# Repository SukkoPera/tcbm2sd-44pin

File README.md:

# TCBM2SD 44-pin
TCBM2SD is a CBM 1551 paddle replacement and/or mass storage device using an SD card interfacing with the Commodore C16/116/Plus4 simulating a TCBM bus 1551 disk drive.

## Summary
This is a 44-pin variant of [the original project by Maciej 'YTM/Elysium' Witkowiak](https://github.com/ytmytm/plus4-tcbm2sd).

This version is still aimed at the C16/C116/Plus4 and it **requires** the usage of a [Plus4MultiExpander](https://github.com/SukkoPera/Plus4MultiExpander) or something similar. It is NOT compatible with the C64/C128.

Isn't Open Hardware great?

## Usage
This variant of the board requires the FPGA to be flashed with the JED file from this project. The corresponding sources are available in the [hdl](hdl/) directory.

Apart from that, please refer to [the original project](https://github.com/ytmytm/plus4-tcbm2sd) for documentation, instructions, etc.

## Releases
If you want to get this board produced, you are recommended to get [the latest release](https://github.com/SukkoPera/tcbm2sd-44pin/releases) rather than the current git version, as the latter might be under development and is not guaranteed to be working.

Every release is accompanied by its Bill Of Materials (BOM) file and any relevant notes about it, which you are recommended to read carefully.

## License
TCBM2SD is licensed under the [Creative Commons Attribution-ShareAlike 4.0 International License](https://creativecommons.org/licenses/by-sa/4.0/).

This documentation is distributed *as is* and WITHOUT ANY EXPRESS OR IMPLIED WARRANTIES whatsoever with respect to its functionality, operability or use, including, without limitation, any implied warranties OF MERCHANTABILITY, SATISFACTORY QUALITY, FITNESS FOR A PARTICULAR PURPOSE or infringement. We expressly disclaim any liability whatsoever for any direct, indirect, consequential, incidental or special damages, including, without limitation, lost revenues, lost profits, losses resulting from business interruption or loss of data, regardless of the form of action or legal theory under which the liability may be asserted, even if advised of the possibility or likelihood of such damages.

## Thanks
- Thanks to Maciej for his amazing work and support.
- 3D model of Arduino Pro Micro by [Toby](https://grabcad.com/library/arduino-pro-mini-5v-16mhz-1).

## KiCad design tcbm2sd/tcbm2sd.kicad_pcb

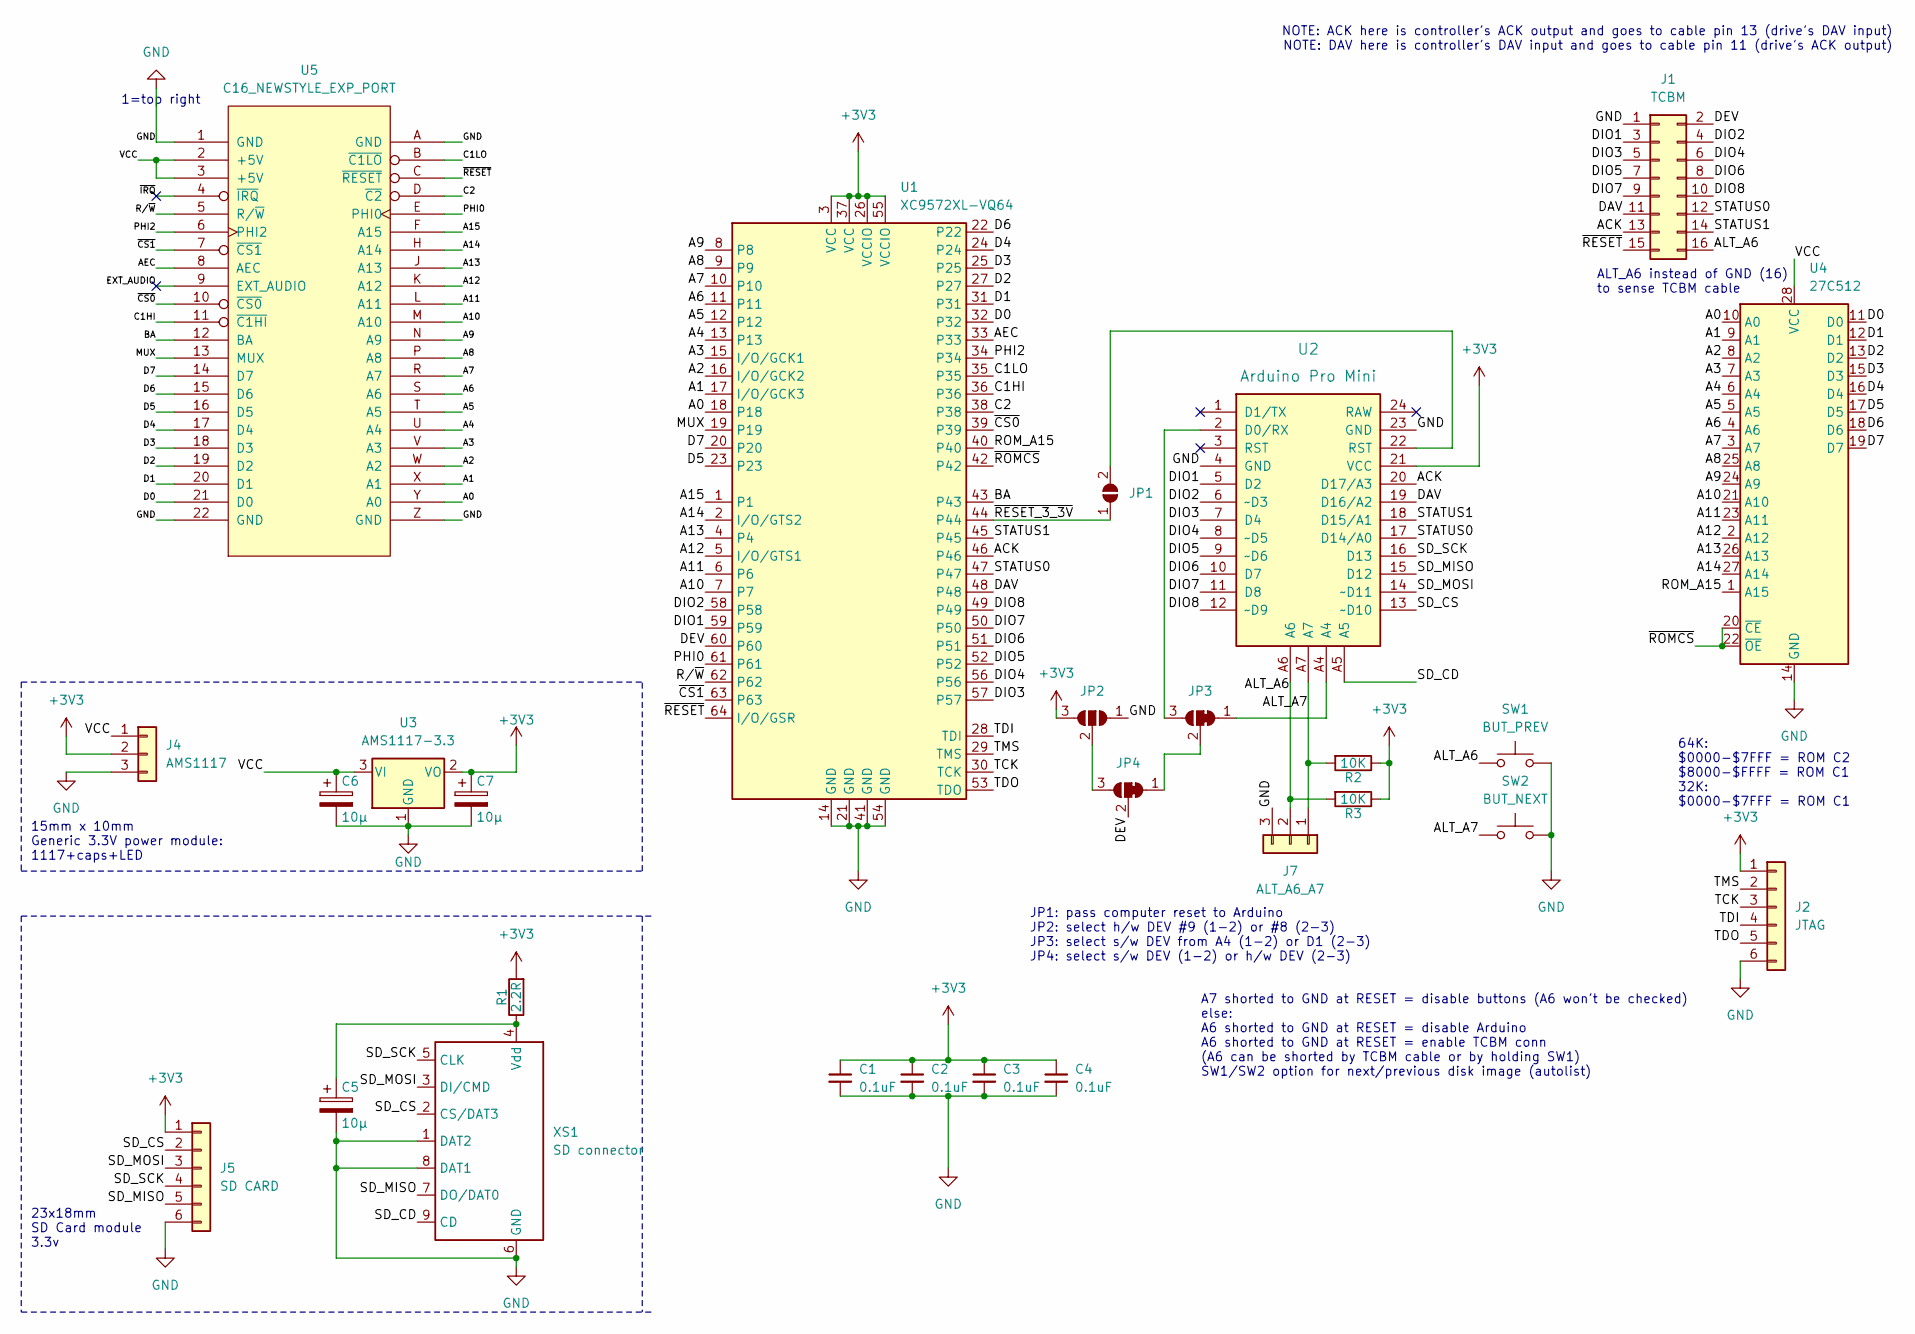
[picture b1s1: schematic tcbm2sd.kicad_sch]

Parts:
C1, C2, C3, C4: 0.1uF; C_0805_2012Metric_Pad1.18x1.45mm_HandSolder; JLCPCB Part # C49678
C5, C6, C7: 10µ; CP_EIA-3216-12_Kemet-S_Pad1.58x1.35mm_HandSolder; JLCPCB Part # C1969735
J1: TCBM; PinHeader_2x08_P2.54mm_Vertical
J2: JTAG; PinHeader_1x06_P2.54mm_Vertical
J4: AMS1117; PinHeader_1x03_P2.54mm_Vertical
J5: SD CARD; PinHeader_1x06_P2.54mm_Vertical
J7: ALT_A6_A7; PinHeader_1x03_P2.54mm_Vertical
JP1: SolderJumper_2_Open; SolderJumper-2_P1.3mm_Open_Pad1.0x1.5mm
JP2: SolderJumper_3_Open; SolderJumper-3_P1.3mm_Open_Pad1.0x1.5mm_NumberLabels
JP3, JP4: SolderJumper_3_Bridged12; SolderJumper-3_P1.3mm_Bridged12_Pad1.0x1.5mm_NumberLabels
R1: 2.2R; R_0805_2012Metric_Pad1.20x1.40mm_HandSolder; JLCPCB Part # C17521
R2, R3: 10K; R_0805_2012Metric_Pad1.20x1.40mm_HandSolder; JLCPCB Part # C17414
SW1: BUT_PREV; SW_PUSH_6mm_OR_SW_Tactile_SPST_Angled_PTS645Vx58-2LFS
SW2: BUT_NEXT; SW_PUSH_6mm_OR_SW_Tactile_SPST_Angled_PTS645Vx58-2LFS
U1: XC9572XL-VQ64; TQFP-64_10x10mm_P0.5mm; JLCPCB Part # C90569
U2: Arduino Pro Mini; Arduino_Pro_Mini
U3: AMS1117-3.3; SOT-223-3_TabPin2; JLCPCB Part # C6186
U4: 27C512; DIP-28_W15.24mm_Socket
U5: C16_NEWSTYLE_EXP_PORT; EdgeConn-44pin
XS1: SD connector; Conn_uSDcard; JLCPCB Part # C7529389

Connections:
+3V3: C1.1, C2.1, C3.1, C4.1, C7.1, J2.1, J4.2, J5.1, JP2.3 (B), R1.2, R2.1, R3.1, U1.3 (VCC), U1.26 (VCCIO), U1.37 (VCC), U1.55 (VCCIO), U2.21 (VCC), U3.2 (VO)
/A0: U1.18, U4.10 (A0), U5.Y (A0)
/A1: U1.17 (I/O/GCK3), U4.9 (A1), U5.X (A1)
/A2: U1.16 (I/O/GCK2), U4.8 (A2), U5.W (A2)
/A3: U1.15 (I/O/GCK1), U4.7 (A3), U5.V (A3)
/A4: U1.13, U4.6 (A4), U5.U (A4)
/A5: U1.12, U4.5 (A5), U5.T (A5)
/A6: U1.11, U4.4 (A6), U5.S (A6)
/A7: U1.10, U4.3 (A7), U5.R (A7)
/A8: U1.9, U4.25 (A8), U5.P (A8)
/A9: U1.8, U4.24 (A9), U5.N (A9)
/A10: U1.7, U4.21 (A10), U5.M (A10)
/A11: U1.6, U4.23 (A11), U5.L (A11)
/A12: U1.5 (I/O/GTS1), U4.2 (A12), U5.K (A12)
/A13: U1.4, U4.26 (A13), U5.J (A13)
/A14: U1.2 (I/O/GTS2), U4.27 (A14), U5.H (A14)
/A15: U1.1, U5.F (A15)
/ACK: J1.13, U1.46, U2.20 (D17/A3)
/AEC: U1.33, U5.8 (AEC)
/ALT_A6: J1.16, J7.2, R3.2, SW1.1, U2.A6
/ALT_A7: J7.1, R2.2, SW2.1, U2.A7
/BA: U1.43, U5.12 (BA)
/C1HI: U1.36, U5.11 (~C1HI)
/C1LO: U1.35, U5.B (~C1LO)
/C2: U1.38, U5.D (~C2)
/D0: U1.32, U4.11 (D0), U5.21 (D0)
/D1: U1.31, U4.12 (D1), U5.20 (D1)
/D2: U1.27, U4.13 (D2), U5.19 (D2)
/D3: U1.25, U4.15 (D3), U5.18 (D3)
/D4: U1.24, U4.16 (D4), U5.17 (D4)
/D5: U1.23, U4.17 (D5), U5.16 (D5)
/D6: U1.22, U4.18 (D6), U5.15 (D6)
/D7: U1.20, U4.19 (D7), U5.14 (D7)
/DAV: J1.11, U1.48, U2.19 (D16/A2)
/DEV: J1.2, JP4.2 (C), U1.60
/DIO1: J1.3, U1.59, U2.5 (D2)
/DIO2: J1.4, U1.58, U2.6 (~D3)
/DIO3: J1.5, U1.57, U2.7 (D4)
/DIO4: J1.6, U1.56, U2.8 (~D5)
/DIO5: J1.7, U1.52, U2.9 (~D6)
/DIO6: J1.8, U1.51, U2.10 (D7)
/DIO7: J1.9, U1.50, U2.11 (D8)
/DIO8: J1.10, U1.49, U2.12 (~D9)
/EXT_AUDIO: U5.9 (EXT_AUDIO)
/MUX: U1.19, U5.13 (MUX)
/PHI0: U1.61, U5.E (PHI0)
/PHI2: U1.34, U5.6 (PHI2)
/ROM_A15: U1.40, U4.1 (A15)
/R/~W: U1.62, U5.5 (R/~W)
/SD_CD: U2.A5, XS1.9 (CD)
/SD_CS: J5.2, U2.13 (~D10), XS1.2 (CS/DAT3)
/SD_MISO: J5.5, U2.15 (D12), XS1.7 (DO/DAT0)
/SD_MOSI: J5.3, U2.14 (~D11), XS1.3 (DI/CMD)
/SD_SCK: J5.4, U2.16 (D13), XS1.5 (CLK)
/STATUS0: J1.12, U1.47, U2.17 (D14/A0)
/STATUS1: J1.14, U1.45, U2.18 (D15/A1)
/TCK: J2.3, U1.30 (TCK)
/TDI: J2.4, U1.28 (TDI)
/TDO: J2.5, U1.53 (TDO)
/TMS: J2.2, U1.29 (TMS)
/VCC: C6.1, J4.1, U3.3 (VI), U4.28 (VCC), U5.2 (+5V), U5.3 (+5V)
/~CS0: U1.39, U5.10 (~CS0)
/~CS1: U1.63, U5.7 (~CS1)
/~IRQ: U5.4 (~IRQ)
/~RESET_3_3V: JP1.1 (A), U1.44
/~RESET: J1.15, U1.64 (I/O/GSR), U5.C (~RESET)
/~ROMCS: U1.42, U4.20 (~CE), U4.22 (~OE)
GND: C1.2, C2.2, C3.2, C4.2, C5.2, C6.2, C7.2, J1.1, J2.6, J4.3, J5.6, J7.3, JP2.1 (A), SW1.2, SW2.2, U1.14 (GND), U1.21 (GND), U1.41 (GND), U1.54 (GND), U2.4 (GND), U2.23 (GND), U3.1 (GND), U4.14 (GND), U5.1 (GND), U5.22 (GND), U5.A (GND), U5.Z (GND), XS1.1 (DAT2), XS1.6 (GND), XS1.8 (DAT1)
unnamed: JP1.2 (B), U2.22 (RST)
unnamed: JP2.2 (C), JP4.3 (B)
unnamed: JP3.1 (A), U2.A4
unnamed: JP3.3 (B), U2.2 (D0/RX)
unnamed: JP3.2 (C), JP4.1 (A)
unnamed: C5.1, R1.1, XS1.4 (Vdd)

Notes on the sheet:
ALT_A6 instead of GND (16) to sense TCBM cable
15mm x 10mm Generic 3.3V power module: 1117+caps+LED
JP1: pass computer reset to Arduino JP2: select h/w DEV #9 (1-2) or #8 (2-3) JP3: select s/w DEV from A4 (1-2) or D1 (2-3) JP4: select s/w DEV (1-2) or h/w DEV (2-3)
A7 shorted to GND at RESET = disable buttons (A6 won't be checked) else: A6 shorted to GND at RESET = disable Arduino A6 shorted to GND at RESET = enable TCBM conn (A6 can be shorted by TCBM cable or by holding SW1) SW1/SW2 option for next/previous disk image (autolist)
NOTE: ACK here is controller's ACK output and goes to cable pin 13 (drive's DAV input) NOTE: DAV here is controller's DAV input and goes to cable pin 11 (drive's ACK output)
1=top right
23x18mm SD Card module 3.3v
64K: $0000-$7FFF = ROM C2 $8000-$FFFF = ROM C1 32K: $0000-$7FFF = ROM C1

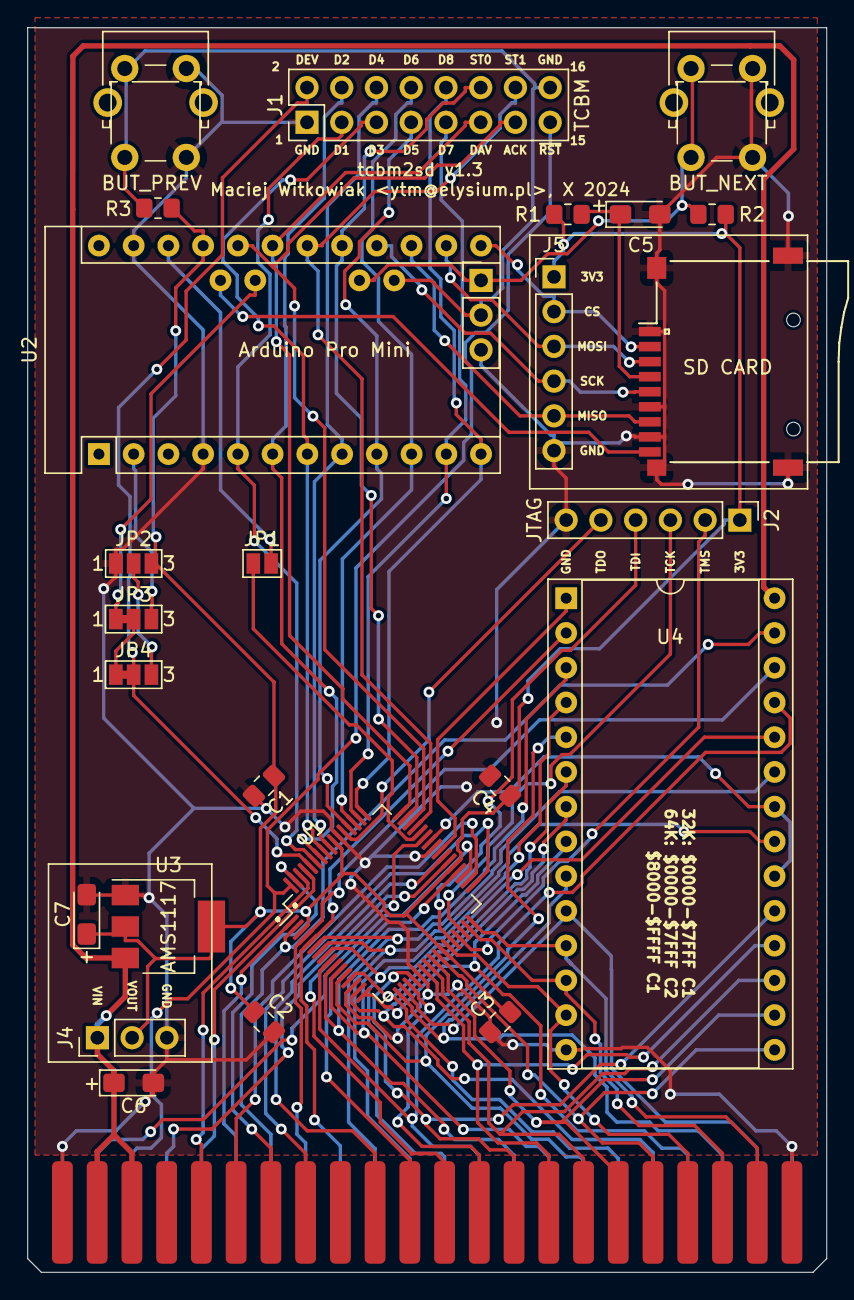
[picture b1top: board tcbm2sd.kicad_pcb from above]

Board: 2 copper layers, 58.4 x 91.0 mm, 27 parts (0 on the bottom side), 72 nets.

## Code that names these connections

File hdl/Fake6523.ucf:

# Fake6523A-28
NET "_reset"		LOC = "P64"  ; # /RESET exp. C
NET "_write"		LOC = "P62"  ; # R/W exp. 5
NET "data<0>"		LOC = "P32"  ; # D0 exp. 21
NET "data<1>"		LOC = "P31"  ; # D1 exp. 20
NET "data<2>"		LOC = "P27"  ; # D2 exp. 19
NET "data<3>"		LOC = "P25"  ; # D3 exp. 18
NET "data<4>"		LOC = "P24"  ; # D4 exp. 17
NET "data<5>"		LOC = "P23"  ; # D5 exp. 16
NET "data<6>"		LOC = "P22"  ; # D6 exp. 15
NET "data<7>"		LOC = "P20"  ; # D7 exp. 14
NET "port_a<0>"	LOC = "P59"  ; # DIO1, <-> wire 3
NET "port_a<1>"	LOC = "P58"  ; # DIO2, <-> wire 4
NET "port_a<2>"	LOC = "P57"  ; # DIO3, <-> wire 5
NET "port_a<3>"	LOC = "P56"  ; # DIO4, <-> wire 6
NET "port_a<4>"	LOC = "P52"  ; # DIO5, <-> wire 7
NET "port_a<5>"	LOC = "P51"  ; # DIO6, <-> wire 8
NET "port_a<6>"	LOC = "P50"  ; # DIO7, <-> wire 9
NET "port_a<7>"	LOC = "P49"  ; # DIO8, <-> wire 10
NET "port_b<0>"	LOC = "P47"  ; # STATUS0, <-, wire 12
NET "port_b<1>"	LOC = "P45"  ; # STATUS1, <-, wire 14
NET "port_c<6>"	LOC = "P46"  ; # ACK, ->, wire 13 (controller's ACK out, drive's DAV in)
NET "port_c<7>"	LOC = "P48"  ; # DAV, <-, wire 11 (controller's DAV in,  drive's ACK out)
NET "rs<0>"			LOC = "P18"  ; # A0 exp. Y
NET "rs<1>"			LOC = "P17"  ; # A1 exp. X
NET "rs<2>"			LOC = "P16"  ; # A2 exp. W

# other inputs
NET "phi2"			LOC = "P34"  ;	# Phi2 exp. 24
NET "aec" 			LOC = "P33"  ; # AEC exp. 22
NET "ba"				LOC = "P43"  ; # BA exp. 13

# ROM control
NET "c1lo"			LOC = "P35"	 ; # J3-1			<- C1LO exp. B
NET "c1hi"			LOC = "P36"  ; # J3-2			<- C1HI exp. 6
NET "c2"				LOC = "P38"  ; # J3-3			<- C2  exp. D (combined C2LO/C2HI)
NET "cs0"			LOC = "P39"  ; # J3-4			<- CS0 exp. 10
NET "rom_a15"		LOC = "P40"  ; # J3-5			-> ROM A15 1
NET "rom_cs"		LOC = "P42"  ; # /CAS			-> ROM /CE/OE 20+22

# PLA inputs
NET "pla_i<1>"		LOC = "P6"	 ; # PLA I1 (8)   <- A11 exp. L
NET "pla_i<2>"		LOC = "P5"	 ; # PLA I2 (7)   <- A12 exp. K
NET "pla_i<3>"    LOC = "P4"	 ; # PLA I3 (6)   <- A13 exp. J
NET "pla_i<4>"		LOC = "P2"	 ; # PLA I4 (5)   <- A14 exp. H
NET "pla_i<5>"		LOC = "P1"	 ; # PLA I5 (4)   <- A15 exp. F
NET "pla_i<6>"		LOC = "P61"  ; # PLA I6 (3)   <- Phi0 exp. E
NET "cs1"			LOC = "P63"	 ; #                 /CS1 exp. 7
NET "pla_i<8>"		LOC = "P60"  ; # PLA I8 (27)  <- DEV signal from device (0 or 1), wire 2
NET "pla_i<9>"    LOC = "P7"   ; # PLA I9 (26)  <- A10 exp. M
NET "pla_i<10>"   LOC = "P19"  ; # PLA I10 (25) <- MUX exp. 12
NET "pla_i<11>"   LOC = "P8"   ; # PLA I11 (24) <- A9 exp. N
NET "pla_i<12>"   LOC = "P9"   ; # PLA I12 (23) <- A8 exp. P
NET "pla_i<13>"   LOC = "P10"  ; # PLA I13 (22) <- A7 exp. R
NET "pla_i<14>"   LOC = "P11"  ; # PLA I14 (21) <- A6 exp. S
NET "pla_i<15>"   LOC = "P12"  ; # PLA I15 (20) <- A5 exp. T
# additional inputs
NET "addr<4>"     LOC = "P13"  ; # PLA xxx      <- A4 exp. U
NET "addr<3>"     LOC = "P15"  ; # PLA xxx      <- A3 exp. V
# additional output (temp. disabled)
NET "_resetout"   LOC = "P44"  ; # copy 5V /RESET to 3.3V /RESET

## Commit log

2025-08-19 Switch to 44-pin connector
2025-08-20 Retouching
2025-10-14 Remove all files that should be taken from upstream
2025-10-14 Update HDL files for 44-pin changes Namely: - Pin 38 = /C2 (new signal) - Pin 39 = /CS0 - Pin 63 = /CS1 - /C2LO = /C2 or /CS0 - /C2HI = /C2 or /CS1
2026-03-03 Fix 3D model
2026-03-03 Update top render
